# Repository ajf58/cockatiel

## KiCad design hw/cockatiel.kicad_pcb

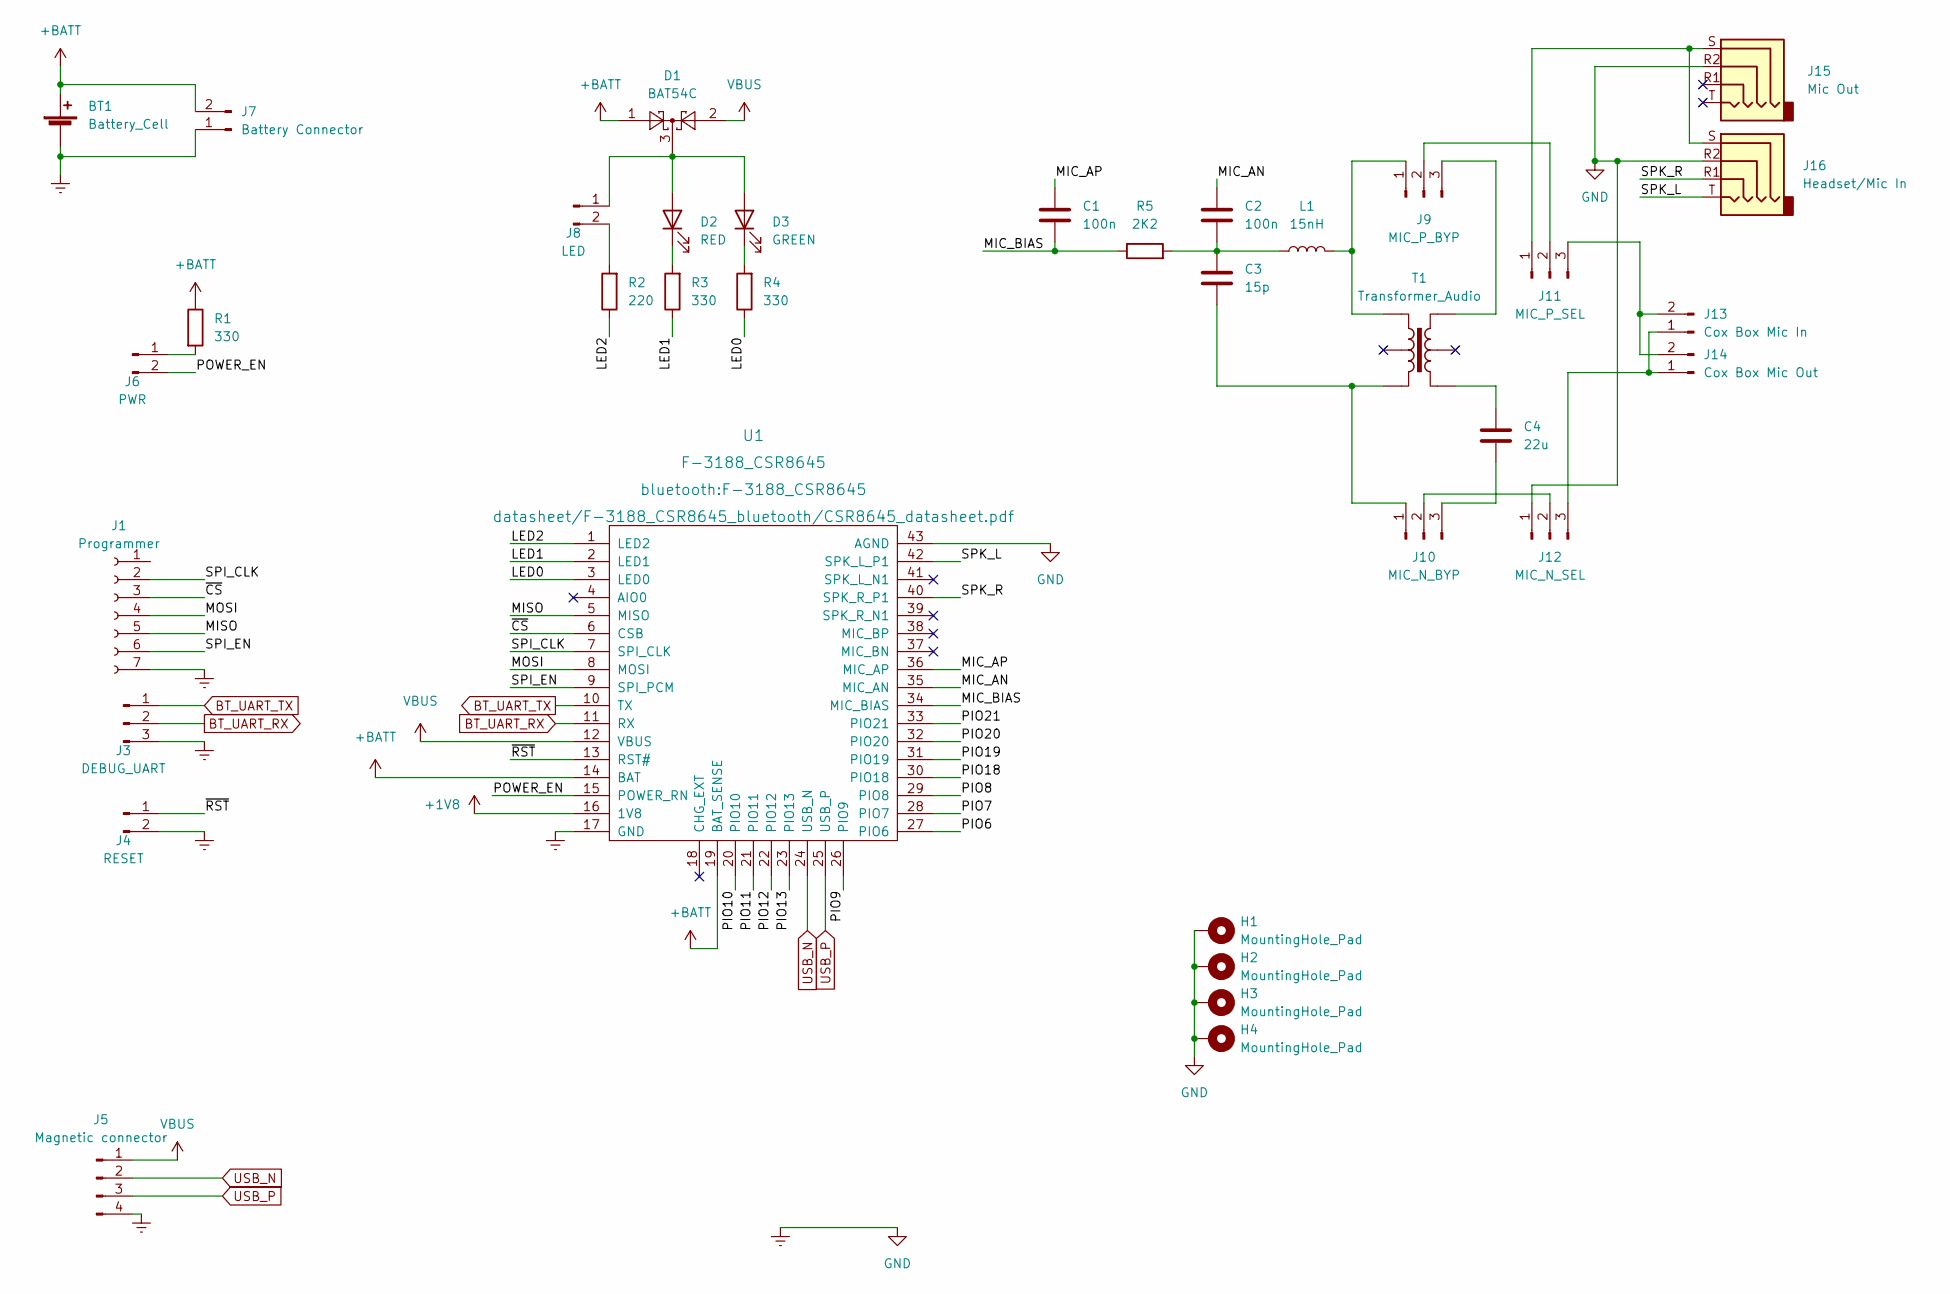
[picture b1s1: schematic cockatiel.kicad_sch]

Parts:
BT1: Battery_Cell
C1, C2: 100n; C_0805_2012Metric_Pad1.18x1.45mm_HandSolder; LCSC C49678
C3: 15p; C_0805_2012Metric_Pad1.18x1.45mm_HandSolder; LCSC C107110
C4: 22u; C_1206_3216Metric_Pad1.33x1.80mm_HandSolder; LCSC C5672
D1: BAT54C; SOT-23; LCSC C37704
D2: RED; LED_0603_1608Metric_Pad1.05x0.95mm_HandSolder; LCSC C2286
D3: GREEN; LED_0603_1608Metric_Pad1.05x0.95mm_HandSolder; LCSC C72043
H1, H2, H3, H4: MountingHole_Pad; MountingHole_3.2mm_M3_Pad_TopBottom
J1: Programmer; PinSocket_1x07_P2.54mm_Vertical; LCSC C492406
J3: DEBUG_UART; PinHeader_1x03_P2.54mm_Vertical; LCSC C49257
J4: RESET; PinHeader_1x02_P2.54mm_Vertical; LCSC C492401
J5: Magnetic connector; PinHeader_1x04_P2.54mm_Vertical; LCSC C225479
J6: PWR; PinHeader_1x02_P2.54mm_Vertical; LCSC C492401
J7: Battery Connector; JST_PH_S2B-PH-K_1x02_P2.00mm_Horizontal; LCSC C173752
J8: LED; PinHeader_1x02_P2.54mm_Vertical; LCSC C492401
J9: MIC_P_BYP; PinHeader_1x03_P2.54mm_Vertical; LCSC C49257
J10: MIC_N_BYP; PinHeader_1x03_P2.54mm_Vertical; LCSC C49257
J11: MIC_P_SEL; PinHeader_1x03_P2.54mm_Vertical; LCSC C49257
J12: MIC_N_SEL; PinHeader_1x03_P2.54mm_Vertical; LCSC C49257
J13: Cox Box Mic In; PinHeader_1x02_P2.54mm_Vertical; LCSC C492401
J14: Cox Box Mic Out; PinHeader_1x02_P2.54mm_Vertical; LCSC C492401
J15: Mic Out; Jack_3.5mm_PJ320D_Horizontal; LCSC C95562
J16: Headset/Mic In; Jack_3.5mm_PJ320D_Horizontal; LCSC C95562
L1: 15nH; L_0402_1005Metric_Pad0.77x0.64mm_HandSolder; LCSC C27143
R1, R3, R4: 330; R_0805_2012Metric_Pad1.20x1.40mm_HandSolder; LCSC C17630
R2: 220; R_0805_2012Metric_Pad1.20x1.40mm_HandSolder; LCSC C17557
R5: 2K2; R_0805_2012Metric_Pad1.20x1.40mm_HandSolder; LCSC C17520
T1: Transformer_Audio; Transformer_Triad_T Y-141PN
U1: F-3188_CSR8645

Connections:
+1V8: U1.16 (1V8)
+BATT: BT1.1 (+), D1.1, J7.2, R1.1, U1.14 (BAT), U1.19 (BAT_SENSE)
/LED0: R4.1, U1.3 (LED0)
/LED1: R3.1, U1.2 (LED1)
/LED2: R2.1, U1.1 (LED2)
/MIC_AN: C2.1, U1.35 (MIC_AN)
/MIC_AP: C1.1, U1.36 (MIC_AP)
/MIC_BIAS: C1.2, R5.1, U1.34 (MIC_BIAS)
/MISO: J1.5, U1.5 (MISO)
/MOSI: J1.4, U1.8 (MOSI)
/PIO6: U1.27 (PIO6)
/PIO7: U1.28 (PIO7)
/PIO8: U1.29 (PIO8)
/PIO9: U1.26 (PIO9)
/PIO10: U1.20 (PIO10)
/PIO11: U1.21 (PIO11)
/PIO12: U1.22 (PIO12)
/PIO13: U1.23 (PIO13)
/PIO18: U1.30 (PIO18)
/PIO19: U1.31 (PIO19)
/PIO20: U1.32 (PIO20)
/PIO21: U1.33 (PIO21)
/POWER_EN: J6.2, U1.15 (POWER_RN)
/SPI_CLK: J1.2, U1.7 (SPI_CLK)
/SPI_EN: J1.6, U1.9 (SPI_PCM)
/SPK_L: J16.T, U1.42 (SPK_L_P1)
/SPK_R: J16.R1, U1.40 (SPK_R_P1)
/~CS: J1.3, U1.6 (CSB)
/~RST: J4.1, U1.13 (RST#)
BT_UART_RX: J3.2, U1.11 (RX)
BT_UART_TX: J3.1, U1.10 (TX)
Earth: BT1.2 (-), H1.1, H2.1, H3.1, H4.1, J1.7, J3.3, J4.2, J5.4, J7.1, J12.1, J15.R2, J16.R2, U1.17 (GND), U1.43 (AGND)
unnamed: C2.2, C3.1, L1.1, R5.2
unnamed: C3.2, J10.1, T1.4
unnamed: C4.1, T1.3
unnamed: C4.2, J10.3
unnamed: D1.3, D2.2 (A), D3.2 (A), J8.1
unnamed: D2.1 (K), R3.2
unnamed: D3.1 (K), R4.2
unnamed: J6.1, R1.2
unnamed: J8.2, R2.2
unnamed: J9.1, L1.2, T1.6
unnamed: J9.3, T1.1
unnamed: J10.2, J12.2
unnamed: J11.1, J15.S, J16.S
unnamed: J9.2, J11.2
unnamed: J11.3, J13.2, J14.2
unnamed: J12.3, J13.1, J14.1
USB_N: J5.2, U1.24 (USB_N)
USB_P: J5.3, U1.25 (USB_P)
VBUS: D1.2, J5.1, U1.12 (VBUS)

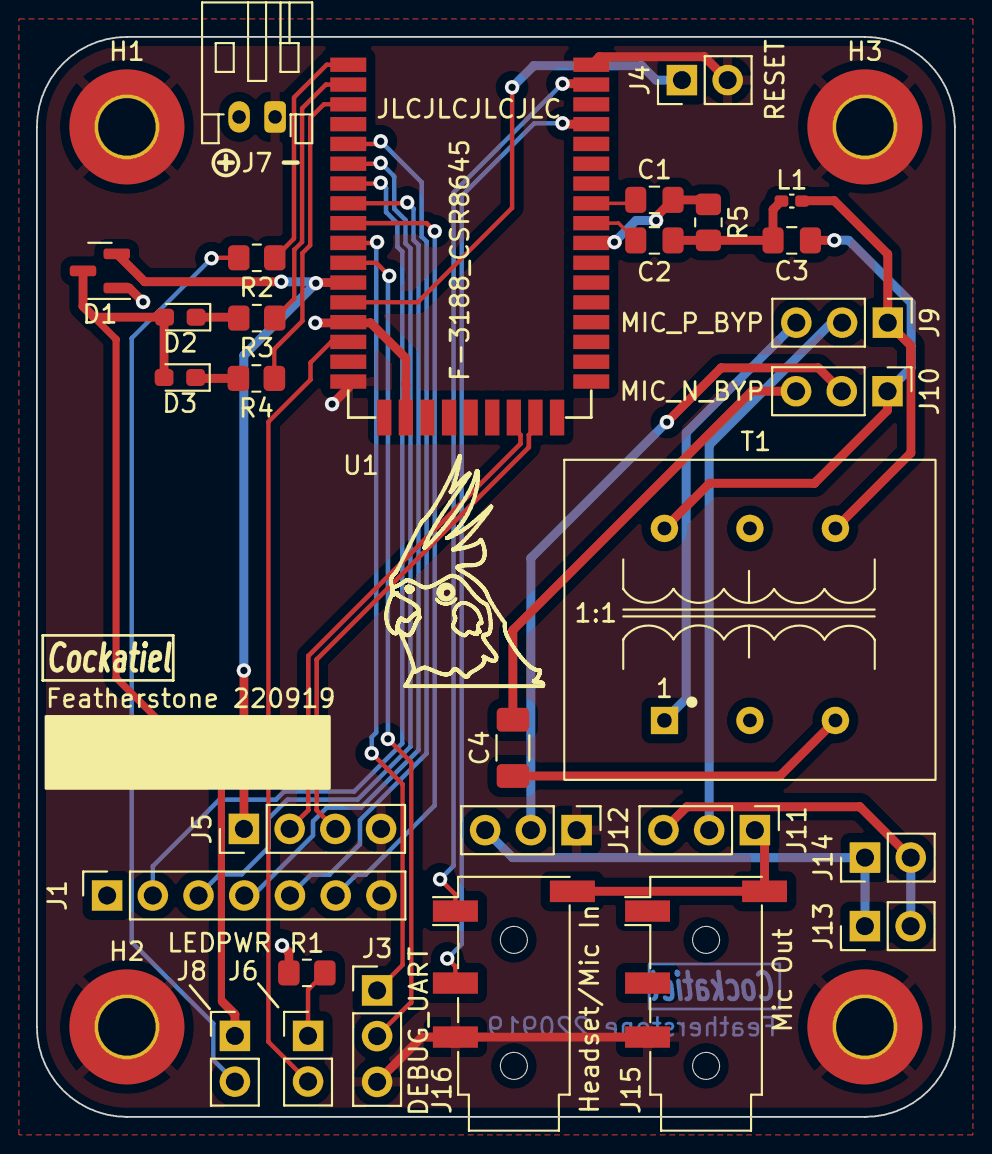
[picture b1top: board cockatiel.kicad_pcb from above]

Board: 4 copper layers, 51.0 x 60.0 mm, 34 parts (0 on the bottom side), 38 nets.

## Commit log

2022-08-12 Add the F-3188 to the circuit diagram.
2022-08-16 Ignore backup files
2022-08-17 Add some power nets and labels for in-use pins
2022-08-27 WIP check-in
    1. Add audio inputs via a TRRS socket (smartphone-style headset).
    2. Add audio passthrough via a second socket.
    3. Support sending audio out on 3.5mm socket headset input.
    4. Add headers for cox's microphone input, and output. This uses
    0.1" pitch headers for now.
    5. Support bypaassing the isolation transformer during development.
2022-08-27 Expose all the PIOs on a debug header.
2022-08-27 Add optional EEPROM
2022-08-28 Add support for external (panel mount) LEDs
    Also correct resistor values to support a set of RGB LEDs.
2022-08-31 Add support for power enable.
2022-08-31 Bring out RST# to a pin header
2022-08-31 Correct alignment of symbols on circuit diagram
2022-08-31 Split the USB D+/D- lines using resistors.
2022-09-01 Bring out the debug UART to a jumper
2022-09-02 Initial work on the board layout
    This includes assigning some LCSC parts for use with JLCPCB.
2022-09-02 Ignore the outputs of the JLCPCB design process
2022-09-13 WIP
    1. Add transformer footprint.
    2. PCB routing
    3. Misc changes to re-add JLCPCB part numbers.
2022-09-17 Complete board layout and JLCPCB component allocation.
2022-09-19 Add a cockatiel logo
2022-09-19 Less body in the logo
    Reduce size, and increase line thickness.
2022-09-19 Correct typo
2022-09-19 Several improvements to board layout:
    1. Fill front and back copper with ground pour.
    2. Add information about the product into the back copper.
    3. Add cockatiel logo to the silkscreen.
    4. Update build date string/version.
2022-09-19 Correct project-specific library setup and spelling
2022-09-20 Update part allocation
2022-09-20 Replace out of stock component with suitable equivalent
2022-10-13 WIP: reduce the board complexity and size
    This in turn reduces the eBoM and board size, aiming to reduce cost of
    manufacture.
2022-10-13 Swap the battery connector pins
    It seems that the de-facto setup is with pin 1 as ground, so fix it
    here.
2022-10-24 Add PSKeys dump to version control
2022-10-27 Add an application-specific PSR file
    Make the device always discoverable.
2022-10-27 Change the Device Name to 'Cockatiel'
2022-10-28 Enter discoverable mode at power on
2022-11-06 Swap pin assignment for the battery connector
    It seems most Li-Po batteries are wired this way round.
2022-11-06 Enable the power swtich LED on power on
2022-11-06 Enable the power switch LED on power off
2022-11-06 Move hardware into its own folder
    This is consistent with the software (sw) folder.
2022-11-06 Remove the 'optional' EEPROM
    The module already has EEPROM fitted. Removing this simplifies board
    layout and size, which will come in handy in the future.
2023-02-20 Update to KiCad 7.0
    No changes to the circuit or layout.
2023-02-20 Add initial CI workflow
2023-02-22 Tenative fix for CI issues by downgrading the checkout action
2023-02-22 Further attempt to unwedge the CI pipeline
    Based on SO the non-root user may be the cause.
2023-02-22 Export the schematic using kicad-cli
2024-07-27 Update to Kicad 8
